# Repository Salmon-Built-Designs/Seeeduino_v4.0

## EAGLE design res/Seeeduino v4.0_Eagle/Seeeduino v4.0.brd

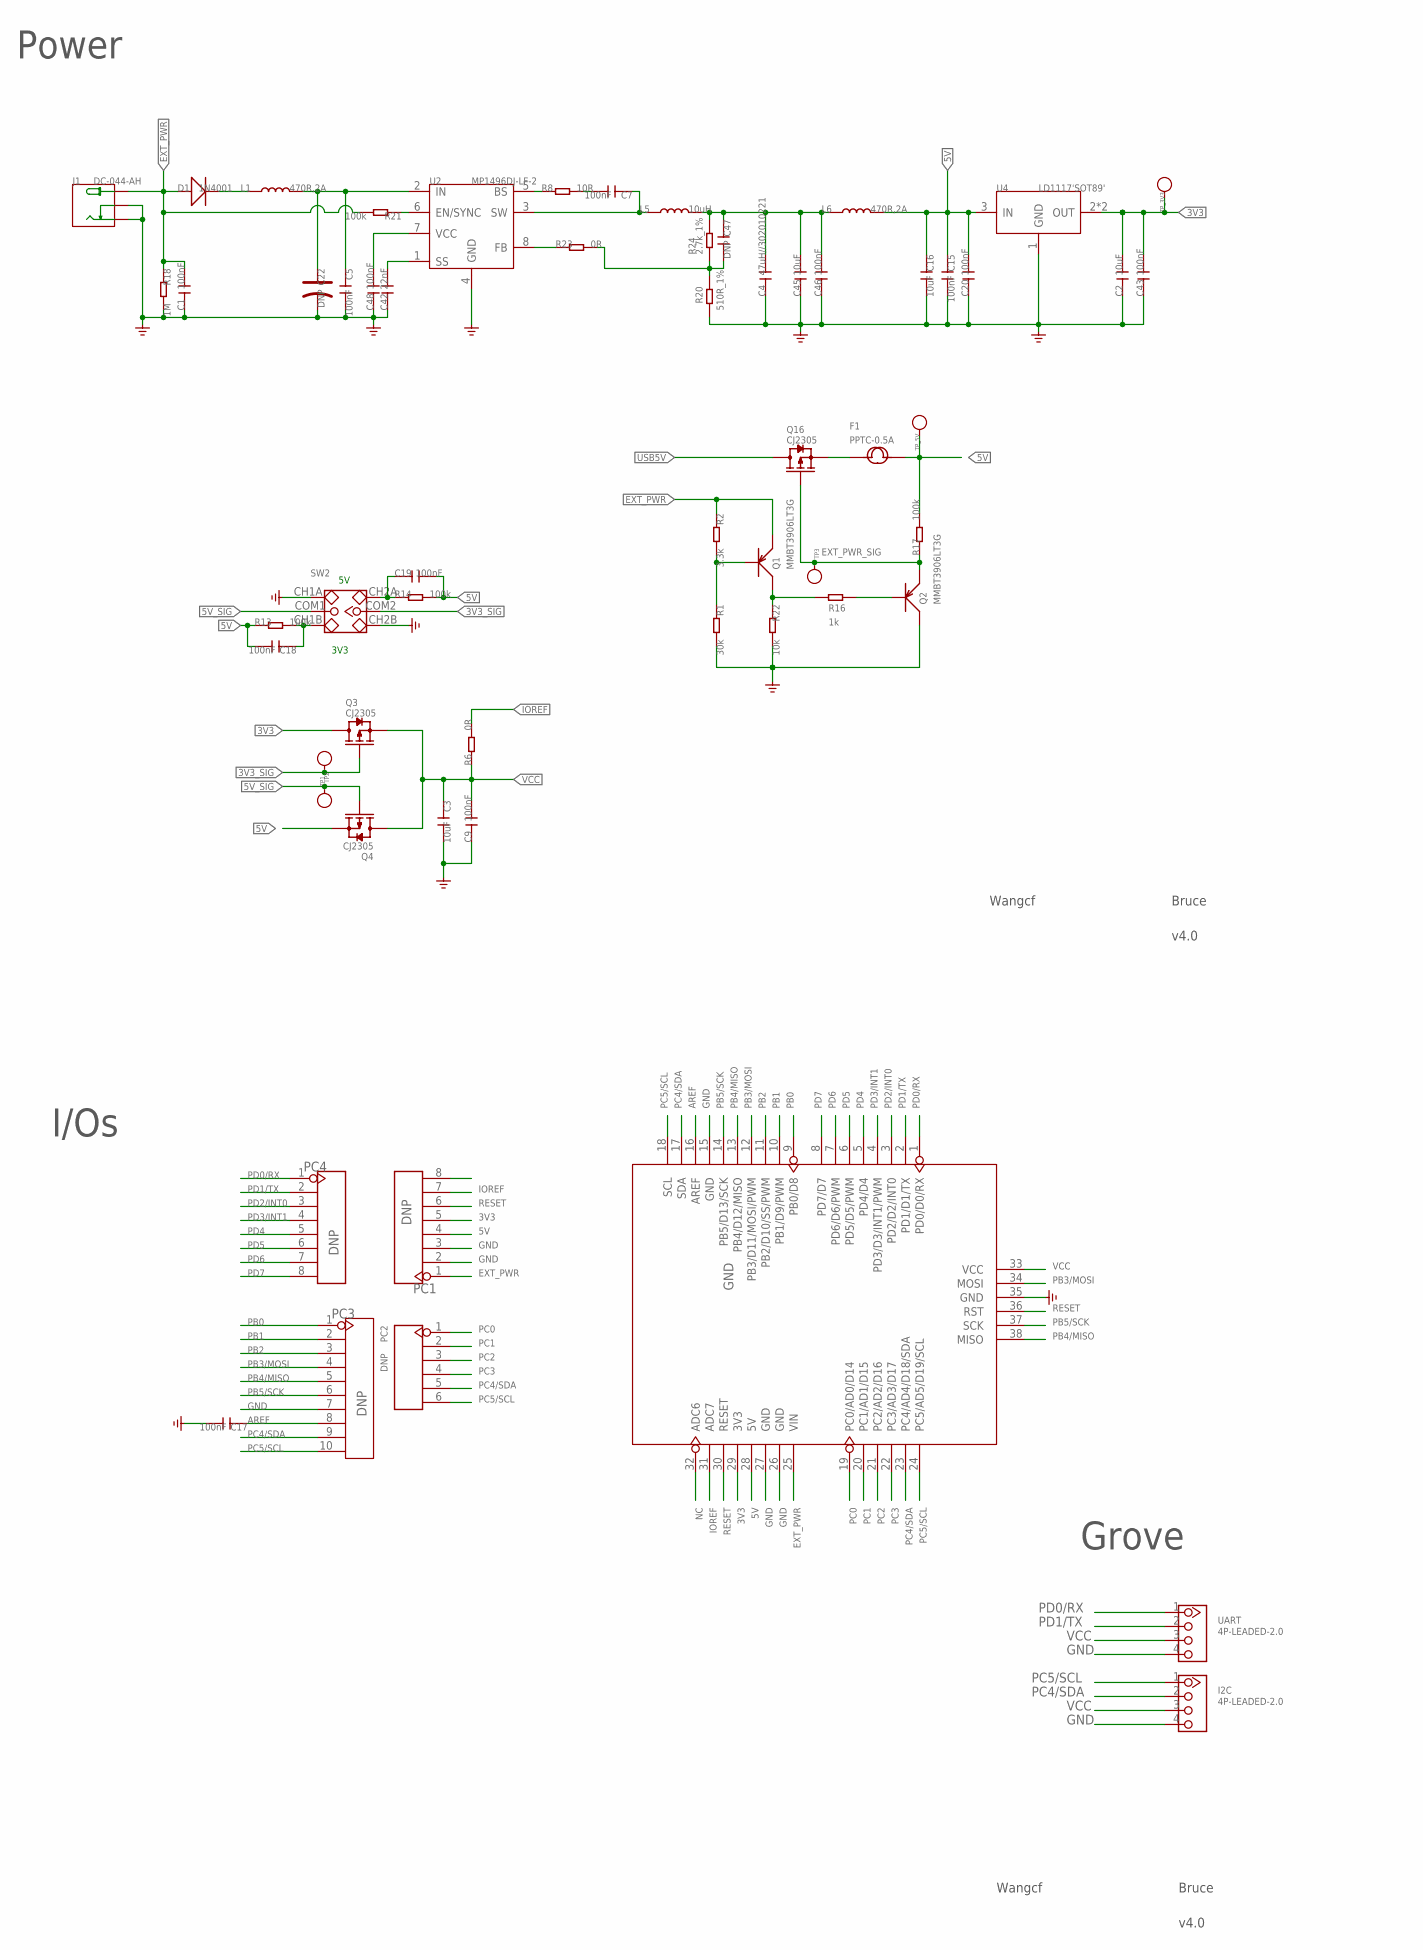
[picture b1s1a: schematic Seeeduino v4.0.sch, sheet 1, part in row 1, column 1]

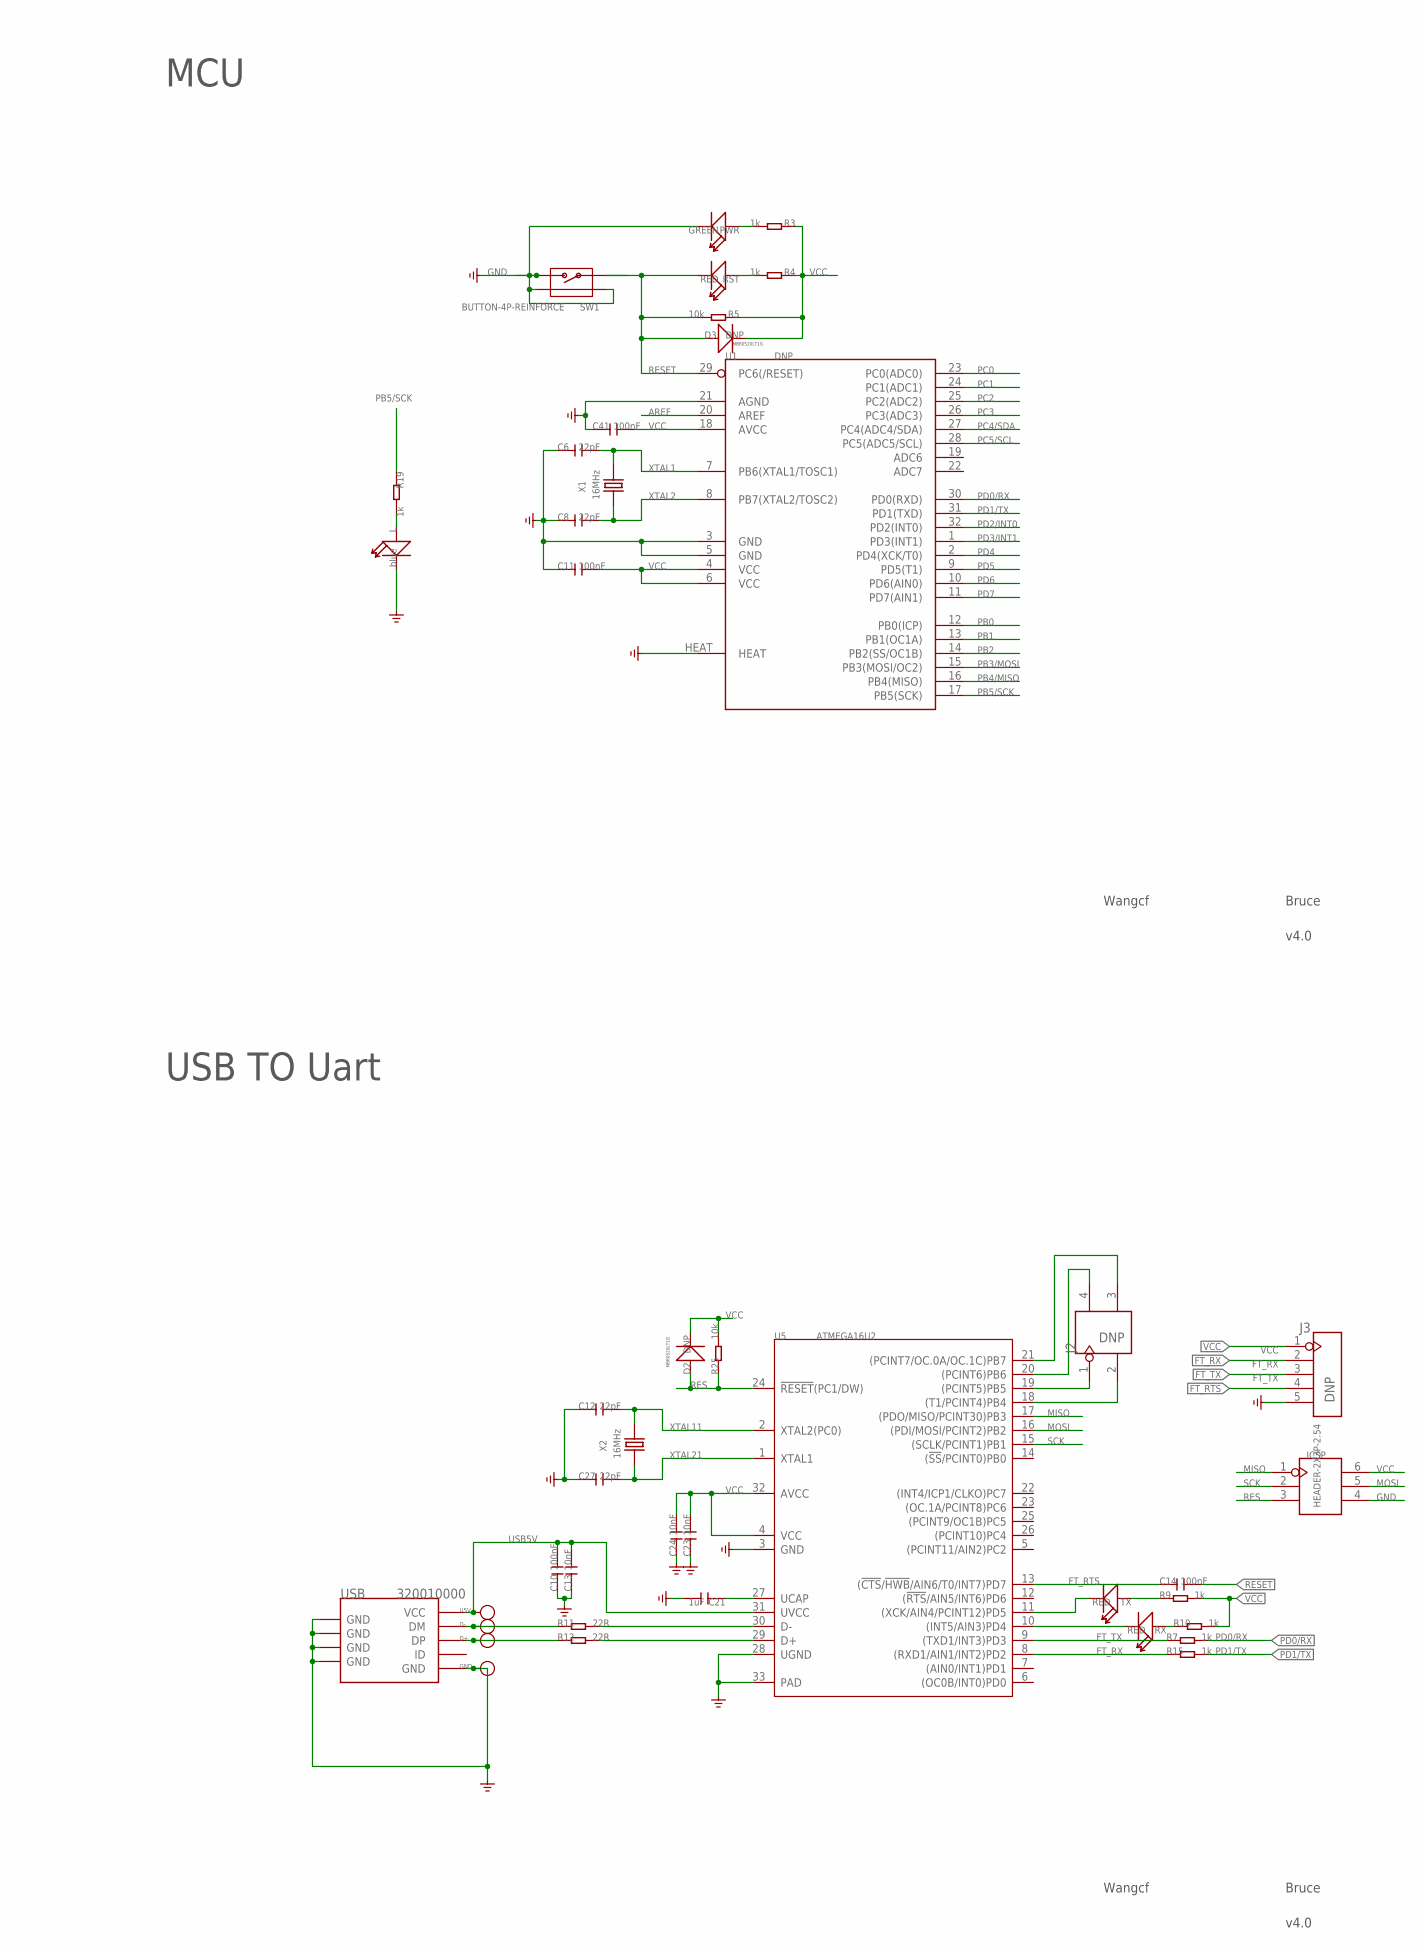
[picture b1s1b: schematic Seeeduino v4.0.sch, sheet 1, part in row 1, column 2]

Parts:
C1, C5, C7, C9, C10, C11, C14, C15, C17, C18, C19, C20, C41, C43, C46, C48: 100nF; C0603
C2, C3, C16, C45: 10uF; C0805
C4: 47uH//302010221; C1206
C6, C8, C12, C27: 22pF; C0603
C13, C23, C24: 10nF; C0603
C21: 1uF; C0603
C22: DNP; AVX-B
C42: 22nF; C0603
C47: DNP; C0603
D1: 1N4001; D2010
D2, D3: DNP; SOD123
D+: PAD-TEST-POINT'4545'; TP_4545
D-: PAD-TEST-POINT'4545'; TP_4545
F1: PPTC-0.5A; F1206
GND: PAD-TEST-POINT'4545'; TP_4545
I2C: 4P-LEADED-2.0
ICSP: HEADER-2X3P-2.54; 2X3P-2.0
J1: DC-044-AH; DC-404
J2: DNP; 2X2P-2.54
J3: DNP; 5P-2.54
L: blue; LED-0603
L1, L6: 470R,2A; L0805
L5: 10uH; 1813
PC1, PC4: DNP; 8P-2.54
PC2: DNP; 6P-2.54-65/35MIL
PC3: DNP; 10P-2.54
PWR: GREEN; LED-0603
Q1, Q2: MMBT3906LT3G; SOT23
Q3, Q4, Q16: CJ2305; SOT23
R1: 30k; R0603
R2: 3.3k; R0603
R3, R4, R7, R9, R10, R15, R16, R19: 1k; R0603
R5, R22, R25: 10k; R0603
R6, R23: 0R; R0603
R8: 10R; R0603
R11, R12: 22R; R0603
R13, R14, R17, R21: 100k; R0603
R18: 1M; R0603
R20: 510R_1%; R0603
R24: 2.7k_1%; R0603
RST: RED; LED-0603
RX: RED; LED-0603
SW1: BUTTON-4P-REINFORCE; 4P-SMD-7X3.5X3.5H
SW2: SWITCH-2CH-6P-2.54; 6P-SMD-2CH-2.54-3.5X7.2
TP1, TP2, TP3: PAD-TEST-POINT'4545'; TP_4545
TP_3V3, TP_5V: PAD-TEST-POINT'4545'; TP_4545
TX: RED; LED-0603
U1: DNP; MLF32X
U2: MP1496DJ-LF-2; TSOT23-8
U3: ARDUINO-38P
U4: LD1117'SOT89'; SOT89
U5: ATMEGA16U2; QFN32
U5V: PAD-TEST-POINT'4545'; TP_4545
UART: 4P-LEADED-2.0
USB: 320010000; MICRO-USB
X1, X2: 16MHz; 2P-SMD-5X3.2

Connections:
3V3: C2.2, C43.2, PC1.5, Q3.3 (D), TP_3V3.T, U3.29 (3V3), U4.2 (OUT), U4.4 (OUT)
3V3_SIG: Q3.1 (G), SW2.COM2, TP1.T
5V: C15.1, C16.1, C18.2, C19.2, C20.2, F1.2, L6.2, PC1.4, Q4.2 (S), R13.1, R14.2, R17.2, TP_5V.T, U3.28 (5V), U4.3 (IN)
5V_SIG: Q4.1 (G), SW2.COM1, TP2.T
AREF: C17.1, PC3.8, U1.20 (AREF), U3.16 (AREF)
D+: D+.T, R12.1, USB.3 (DP)
D-: D-.T, R11.1, USB.2 (DM)
EXT_PWR: C1.2, D1.+, J1.+, PC1.1, Q1.2 (E), R2.1, R18.1, R21.2, U3.25 (VIN)
EXT_PWR_SIG: Q2.2 (E), Q16.1 (G), R17.1, TP3.T
FT_RTS: C14.1, J3.4, U5.13 ((!CTS!/!HWB!/AIN6/T0/INT7)PD7)
FT_RX: J3.2, R15.1, U5.8 ((RXD1/AIN1/INT2)PD2)
FT_TX: J3.3, R7.1, U5.9 ((TXD1/INT3)PD3)
GND: C1.1, C2.1, C3.2, C4.1, C5.2, C6.1, C8.1, C9.1, C10.1, C11.1, C12.1, C13.1, C15.2, C16.2, C17.2, C20.1, C21.2, C22.-, C23.1, C24.1, C27.1, C41.1, C42.1, C43.1, C45.1, C46.1, C48.1, GND.T, I2C.4, ICSP.4, J1.-, J1.CDN, J3.5, L.-, PC1.2, PC1.3, PC3.7, PWR.-, Q2.3 (C), R1.2, R18.2, R20.1, R22.2, SW1.2, SW1.S1, SW1.S2, SW2.CH1A, SW2.CH2B, U1.3 (GND), U1.5 (GND), U1.21 (AGND), U1.HEAT, U2.4 (GND), U3.15 (GND), U3.26 (GND), U3.27 (GND), U3.35 (GND), U4.1 (GND), U5.3 (GND), U5.28 (UGND), U5.33 (PAD), UART.4, USB.5 (GND), USB.S1 (GND), USB.S2 (GND), USB.S3 (GND), USB.S4 (GND), USB.S5 (GND), USB.S6 (GND)
IOREF: PC1.7, R6.2, U3.31 (ADC7)
MISO: ICSP.1, U5.17 ((PDO/MISO/PCINT30)PB3)
MOSI: ICSP.5, U5.16 ((PDI/MOSI/PCINT2)PB2)
unnamed: TX.-, U5.11 ((XCK/AIN4/PCINT12)PD5)
unnamed: L.+, R19.2
unnamed: Q1.1 (B), R1.1, R2.2
unnamed: R11.2, U5.30 (D-)
unnamed: PWR.+, R3.2
unnamed: Q2.1 (B), R16.2
unnamed: Q1.3 (C), R16.1, R22.1
unnamed: D1.-, L1.1
unnamed: C18.1, R13.2, SW2.CH1B
unnamed: R10.1, RX.+
unnamed: R12.2, U5.29 (D+)
unnamed: RX.-, U5.10 ((INT5/AIN3)PD4)
unnamed: C19.1, R14.1, SW2.CH2A
unnamed: J2.1, U5.19 ((PCINT5)PB5)
unnamed: R4.2, RST.+
unnamed: C21.1, U5.27 (UCAP)
unnamed: R21.1, U2.6 (EN/SYNC)
unnamed: C48.2, U2.7 (VCC)
unnamed: C42.2, U2.1 (SS)
unnamed: R8.1, U2.5 (BS)
unnamed: C7.1, L5.1, U2.3 (SW)
unnamed: C7.2, R8.2
unnamed: R23.1, U2.8 (FB)
unnamed: J2.2, U5.18 ((T1/PCINT4)PB4)
unnamed: C47.2, R20.2, R23.2, R24.2
unnamed: J2.4, U5.20 ((PCINT6)PB6)
unnamed: J2.3, U5.21 ((PCINT7/OC.0A/OC.1C)PB7)
unnamed: R9.1, TX.+
NC: PC1.8, U3.32 (ADC6)
OUT1: C4.2, C45.2, C46.2, C47.1, L5.2, L6.1, R24.1
P5V: F1.1, Q16.2 (S)
PB0: PC3.1, U1.12 (PB0(ICP)), U3.9 (PB0/D8)
PB1: PC3.2, U1.13 (PB1(OC1A)), U3.10 (PB1/D9/PWM)
PB2: PC3.3, U1.14 (PB2(SS/OC1B)), U3.11 (PB2/D10/SS/PWM)
PB3/MOSI: PC3.4, U1.15 (PB3(MOSI/OC2)), U3.12 (PB3/D11/MOSI/PWM), U3.34 (MOSI)
PB4/MISO: PC3.5, U1.16 (PB4(MISO)), U3.13 (PB4/D12/MISO), U3.38 (MISO)
PB5/SCK: PC3.6, R19.1, U1.17 (PB5(SCK)), U3.14 (PB5/D13/SCK), U3.37 (SCK)
PC0: PC2.1, U1.23 (PC0(ADC0)), U3.19 (PC0/AD0/D14)
PC1: PC2.2, U1.24 (PC1(ADC1)), U3.20 (PC1/AD1/D15)
PC2: PC2.3, U1.25 (PC2(ADC2)), U3.21 (PC2/AD2/D16)
PC3: PC2.4, U1.26 (PC3(ADC3)), U3.22 (PC3/AD3/D17)
PC4/SDA: I2C.2, PC2.5, PC3.9, U1.27 (PC4(ADC4/SDA)), U3.17 (SDA), U3.23 (PC4/AD4/D18/SDA)
PC5/SCL: I2C.1, PC2.6, PC3.10, U1.28 (PC5(ADC5/SCL)), U3.18 (SCL), U3.24 (PC5/AD5/D19/SCL)
PD0/RX: PC4.1, R7.2, U1.30 (PD0(RXD)), U3.1 (PD0/D0/RX), UART.1
PD1/TX: PC4.2, R15.2, U1.31 (PD1(TXD)), U3.2 (PD1/D1/TX), UART.2
PD2/INT0: PC4.3, U1.32 (PD2(INT0)), U3.3 (PD2/D2/INT0)
PD3/INT1: PC4.4, U1.1 (PD3(INT1)), U3.4 (PD3/D3/INT1/PWM)
PD4: PC4.5, U1.2 (PD4(XCK/T0)), U3.5 (PD4/D4)
PD5: PC4.6, U1.9 (PD5(T1)), U3.6 (PD5/D5/PWM)
PD6: PC4.7, U1.10 (PD6(AIN0)), U3.7 (PD6/D6/PWM)
PD7: PC4.8, U1.11 (PD7(AIN1)), U3.8 (PD7/D7)
PWR_IN: C5.1, C22.+, L1.2, U2.2 (IN)
RES: D2.+, ICSP.3, R25.1, U5.24 (!RESET!(PC1/DW))
RESET: C14.2, D3.+, PC1.6, R5.2, RST.-, SW1.1, U1.29 (PC6(/RESET)), U3.30 (RESET), U3.36 (RST)
SCK: ICSP.2, U5.15 ((SCLK/PCINT1)PB1)
USB5V: C10.2, C13.2, Q16.3 (D), U5.31 (UVCC), U5V.T, USB.1 (VCC)
VCC: C3.1, C9.2, C11.2, C23.2, C24.2, C41.2, D2.-, D3.-, I2C.3, ICSP.6, J3.1, Q3.2 (S), Q4.3 (D), R3.1, R4.1, R5.1, R6.1, R9.2, R10.2, R25.2, U1.4 (VCC), U1.6 (VCC), U1.18 (AVCC), U3.33 (VCC), U5.4 (VCC), U5.32 (AVCC), UART.3
XTAL1: C6.2, U1.7 (PB6(XTAL1/TOSC1)), X1.2
XTAL2: C8.2, U1.8 (PB7(XTAL2/TOSC2)), X1.1
XTAL11: C12.2, U5.2 (XTAL2(PC0)), X2.2
XTAL21: C27.2, U5.1 (XTAL1), X2.1

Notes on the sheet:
I/Os
Grove
USB TO Uart
MCU
Power
MBR0520LT1G
3V3
Wangcf
Bruce
v4.0

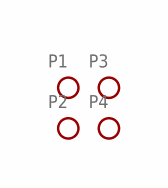
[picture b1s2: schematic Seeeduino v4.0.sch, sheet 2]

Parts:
P1, P2, P3, P4: PAD-MARK; ROUND-MARK-1.0

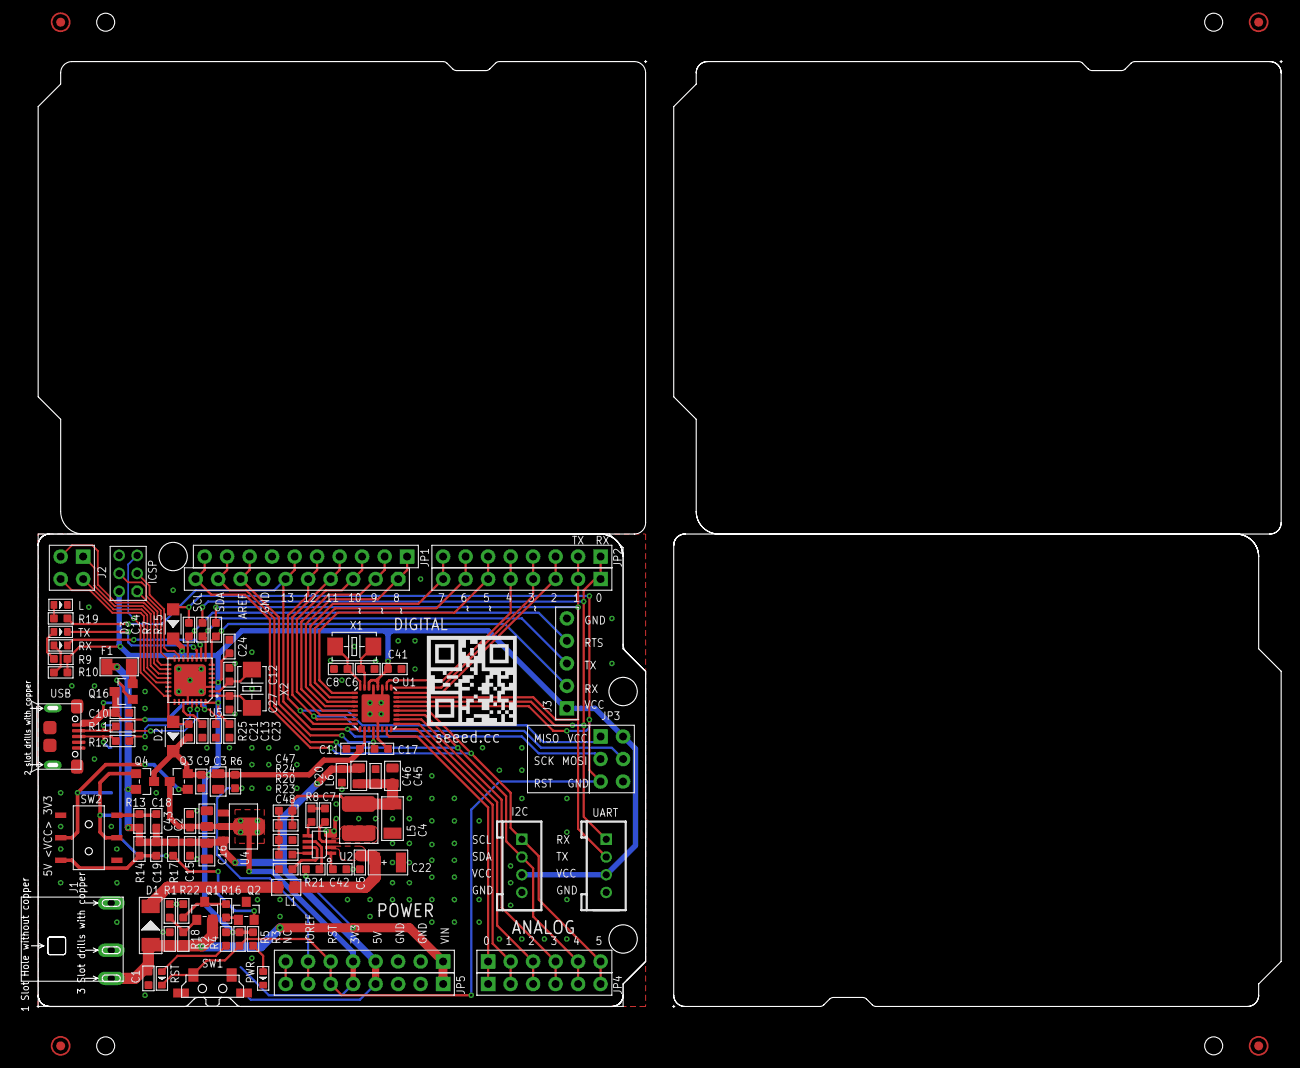
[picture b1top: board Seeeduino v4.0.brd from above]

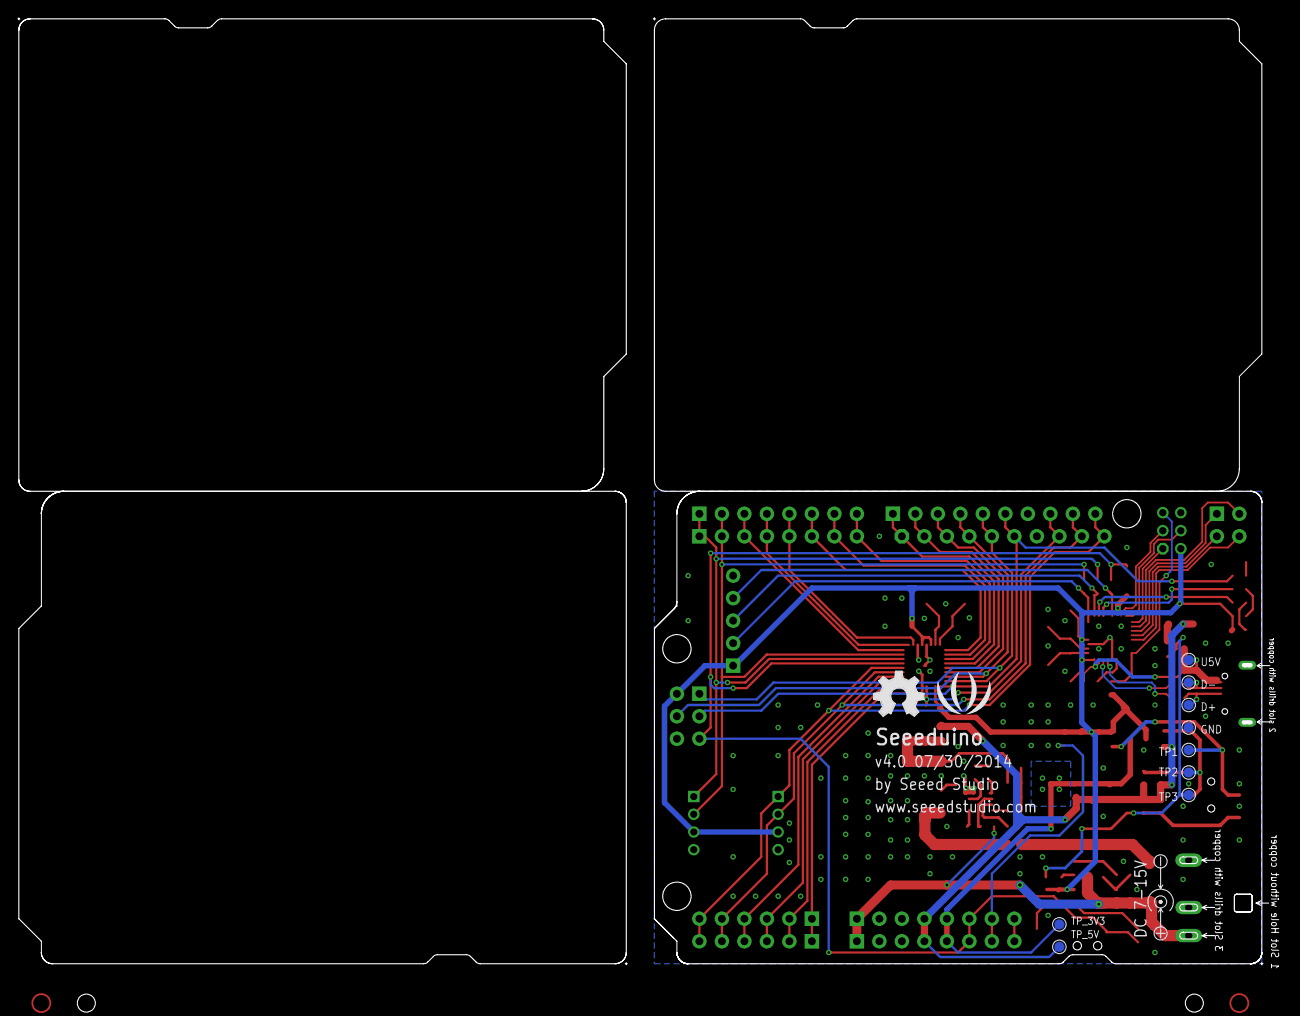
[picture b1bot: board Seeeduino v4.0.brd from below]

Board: 2 copper layers, 142.3 x 110.2 mm, 110 parts (11 on the bottom side), 77 nets.

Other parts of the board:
U$2: SEEED_MASK
U$4: LOGO_SILK
U$5: OSHW_FILLX200_NOTEXT

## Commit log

2017-06-04 upgrade
2019-11-06 add
    add
